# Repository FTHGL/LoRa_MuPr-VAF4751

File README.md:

# Multi-Protocol Hybrid Wireless Communication System (LoRa-GSM-DTMF)

An **STM32-based hybrid communication platform** designed for seamless data and command transmission in environments with limited or no internet infrastructure (disaster management, rural IoT, remote monitoring or etc.). This system integrates low-power **LoRa** technology with **GSM** coverage and **DTMF** control into a single modular architecture.

## Technical Architecture
The system utilizes a hybrid topology consisting of a **Master** node and multiple **Slave** nodes:

* **Master Node:** Features an STM32F103C8T6 MCU, SIM800C GSM module, and RN2483A LoRa module. It acts as the network gateway and central authority.
* **Slave Nodes:** Composed of STM32F103C8T6 and RN2483A modules. These nodes collect sensor data and transmit it to the Master via LoRa.
* **Hybrid Topology:** Operates in a "Star" configuration under normal conditions, with a dynamic shift to a "Mesh" structure using nodes as opportunistic relays when direct access is obstructed.

## Key Features
* **Protocol Bridging:** Real-time translation of commands received via SMS or Command (DTMF) into LoRa packets for end-node execution.
* **Fault Tolerance:** Dynamic routing mechanism allowing slave nodes to reach the master through neighboring nodes if the direct link is lost.
* **Critical Control (DTMF):** Infrastructure-independent device management via voice calls and DTMF tones, bypassing the need for internet or SMS data lines.
* **RF Optimization:** Impedance-controlled transmission lines (50 Ω) and custom antenna structures optimized for 868 MHz and 1.8 GHz bands.

## Hardware Specifications
* **MCU:** STM32F103C8T6 (ARM Cortex-M3).
* **RF Modules:** Microchip RN2483A (LoRa), SIMCom SIM800C (GSM/GPRS/DTMF).
* **Antenna Design:** Integrated IFA (Inverted-F Antenna) for 868 MHz and optimized microstrip structures for 1.8 GHz.
* **PCB Design:** High RF integrity with dedicated ground planes and impedance-matched traces.

## Software Flow
The firmware is modular, managing cross-protocol data flow and task scheduling:
1.  **Ingress:** Command reception and validation via GSM (SMS/DTMF).
2.  **Routing:** Identification of the target `node_id` and LoRa packet encapsulation.
3.  **Transmission:** Delivery of data to the slave node and reporting the response (ACK/Data) back to the user via GSM.

---
*This project was developed as a Graduation Project at Konya Technical University, Department of Electrical and Electronics Engineering.*

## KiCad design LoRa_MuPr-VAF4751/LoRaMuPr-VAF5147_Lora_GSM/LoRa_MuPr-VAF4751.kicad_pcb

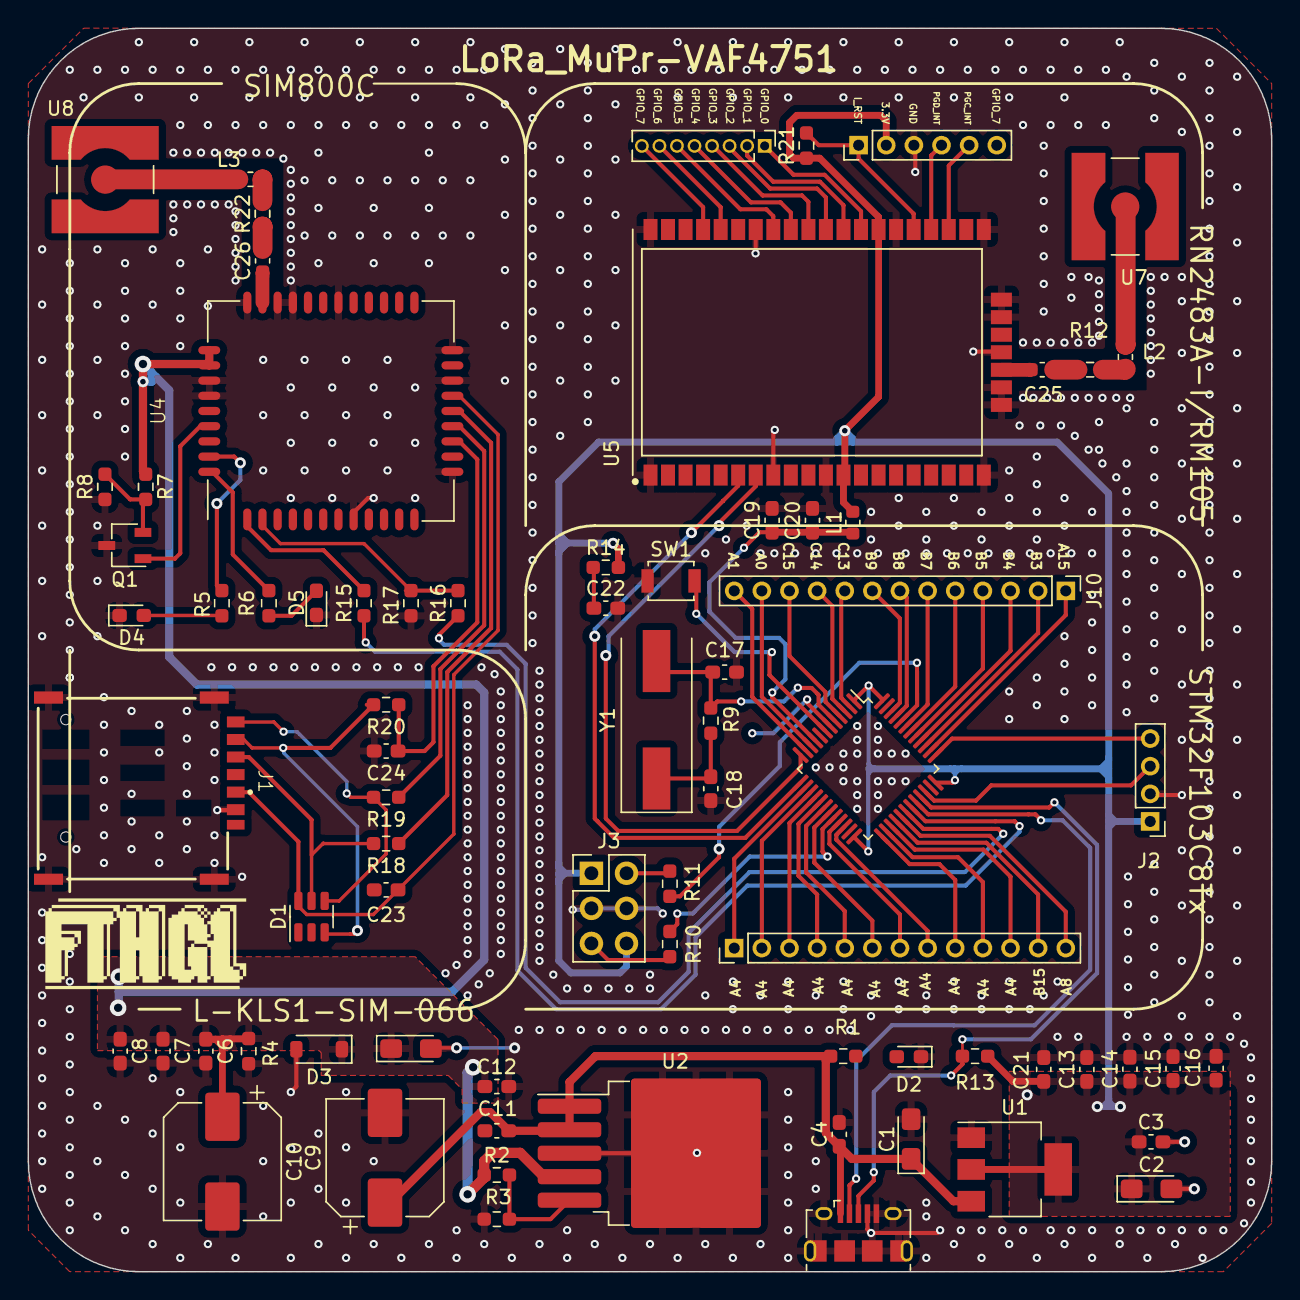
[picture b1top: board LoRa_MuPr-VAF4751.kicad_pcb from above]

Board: 2 copper layers, 90.0 x 90.0 mm, 74 parts (0 on the bottom side), 83 nets.

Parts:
C1, C2: 10uF; CP_EIA-3216-18_Kemet-A_Pad1.58x1.35mm_HandSolder
C3, C4, C13, C14, C15, C16, C20, C22, C23: 100nF; C_0603_1608Metric_Pad1.08x0.95mm_HandSolder
C5: 100uF; CP_EIA-3216-18_Kemet-A_Pad1.58x1.35mm_HandSolder
C6, C12: 10uF; C_0603_1608Metric_Pad1.08x0.95mm_HandSolder
C7: 33pF; C_0603_1608Metric_Pad1.08x0.95mm_HandSolder
C8: 10pF; C_0603_1608Metric_Pad1.08x0.95mm_HandSolder
C9: 100uF; CP_Elec_8x10
C10: 330uF; CP_Elec_8x10
C11, C19: 1uF; C_0603_1608Metric_Pad1.08x0.95mm_HandSolder
C17, C18, C24: 22pF; C_0603_1608Metric_Pad1.08x0.95mm_HandSolder
C21: 4u7F; C_0603_1608Metric_Pad1.08x0.95mm_HandSolder
C25: 9.1pF; C_0603_1608Metric_Pad1.08x0.95mm_HandSolder
C26: 1.8pF; C_0603_1608Metric_Pad1.08x0.95mm_HandSolder
D1: ESDA6V1-5SC6; SOT-23-6
D2, D4, D5: LED; LED_0603_1608Metric_Pad1.05x0.95mm_HandSolder
D3: 5.1V/500mW; D_SOD-123
J1: SIM_Card; L-KLS1-SIM-066
J2: Conn_01x04; PinHeader_1x04_P2.00mm_Vertical
J3: Conn_02x03_Counter_Clockwise; PinHeader_2x03_P2.54mm_Vertical
J5: Conn_01x06; PinHeader_1x06_P2.00mm_Vertical
J6: Conn_01x08; PinHeader_1x08_P1.27mm_Vertical
J10, J11: Conn_01x13; PinHeader_1x13_P2.00mm_Vertical
L1: 27nH; L_0603_1608Metric
L2: 4.7nH; L_0603_1608Metric_Pad1.05x0.95mm_HandSolder
L3: 3.9nH; L_0603_1608Metric_Pad1.05x0.95mm_HandSolder
Q1: BC337; TSOT-23
R1, R5, R6, R10, R11: 1k; R_0603_1608Metric_Pad0.98x0.95mm_HandSolder
R2: 100k; R_0603_1608Metric_Pad0.98x0.95mm_HandSolder
R3: 43k; R_0603_1608Metric_Pad0.98x0.95mm_HandSolder
R4: 470R; R_0603_1608Metric_Pad0.98x0.95mm_HandSolder
R7, R8: 4.7k; R_0603_1608Metric_Pad0.98x0.95mm_HandSolder
R9: 1M; R_0603_1608Metric_Pad0.98x0.95mm_HandSolder
R12, R22: 50R; R_0603_1608Metric_Pad0.98x0.95mm_HandSolder
R13, R14: 1k5; R_0603_1608Metric_Pad0.98x0.95mm_HandSolder
R15, R16: 1K; R_0603_1608Metric_Pad0.98x0.95mm_HandSolder
R17: 5.6K; R_0603_1608Metric_Pad0.98x0.95mm_HandSolder
R18, R19, R20: 51R; R_0603_1608Metric_Pad0.98x0.95mm_HandSolder
R21: 10k; R_0603_1608Metric_Pad0.98x0.95mm_HandSolder
SW1: SW_Push; SW_SPST_B3U-1000P
U1: AMS1117-3.3; SOT-223-3_TabPin2
U2: MIC29302WU; TO-263-5_TabPin3
U3: STM32F103C8Tx; LQFP-48_7x7mm_P0.5mm
U4: SIM800C; SİM800C
U5: RN2483A-I/RM105; MICROCHIP_RN2483
U6: USB_micro-B_amphenol; USB_micro-B_amphenol_101181994_horizontal
U7, U8: LINX_CONSMA001-SMD
Y1: Crystall; Crystal_SMD_HC49-SD

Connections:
3.3V: C2.1, C3.1, C13.1, C14.1, C15.1, C16.1, C21.1, J2.1, J3.1, J3.6, J5.2, L1.1, R13.2, R14.2, R21.1, U1.2 (VO), U3.1 (VBAT), U3.24 (VDD), U3.36 (VDD), U3.48 (VDD), U5.12 (VDD), U5.34 (VDD)
3.3VA: C19.1, C20.1, L1.2, U3.9 (VDDA)
5v: C1.1, C4.1, C9.1, C11.1, R1.1, U1.3 (VI), U2.1 (EN), U2.2 (VIN), U6.1 (VBUS)
BOOT_0: R11.1, U3.44 (BOOT0)
BOOT_1: R10.2, U3.20 (PB2)
GND: C1.2, C2.2, C3.2, C4.2, C5.2, C6.2, C7.2, C8.2, C9.2, C10.2, C11.2, C12.2, C13.2, C14.2, C15.2, C16.2, C17.1, C18.1, C19.2, C20.2, C21.2, C22.2, C23.2, C24.1, D1.2 (GND), D2.1 (K), D3.2 (A), D4.1 (K), D5.1 (K), J1.5 (GND), J2.2, J3.3, J3.4, J5.3, Q1.3 (E), R3.2, R4.2, R8.1, R17.1, SW1.2, U1.1 (GND), U2.3 (GND), U3.8 (VSSA), U3.23 (VSS), U3.35 (VSS), U3.47 (VSS), U4.8 (GND), U4.13 (GND), U4.19 (GND), U4.21 (GND), U4.27 (GND), U4.30 (GND), U4.31 (GND), U4.33 (GND), U4.36 (GND), U4.37 (GND), U5.1 (GND), U5.8 (GND), U5.11 (GND), U5.20 (GND), U5.21 (GND), U5.22 (GND), U5.24 (GND), U5.26 (GND), U5.27 (GND), U5.28 (GND), U5.33 (GND), U5.41 (GND), U5.47 (GND), U6.4 (ID), U6.5 (GND), U6.6 (Shield)
GSM_ANT: C26.1, U4.32 (GSM_ANT)
HSE_OSC_IN: C17.2, R9.1, U3.5 (PD0), Y1.2
HSE_OSC_OUT: C18.2, R9.2, U3.6 (PD1), Y1.1
I_RESET: J5.1, R21.2, U5.32 (*RESET)
L_GPIO0: J6.1, U5.35 (GPIO0)
L_GPIO1: J6.2, U5.36 (GPIO1)
L_GPIO2: J6.3, U5.37 (GPIO2)
L_GPIO3: J6.4, U5.38 (GPIO3)
L_GPIO4: J6.5, U5.39 (GPIO4)
L_GPIO5: J6.6, U5.40 (GPIO5)
L_GPIO6: J6.7, U5.43 (GPIO6)
L_GPIO7: J6.8, U5.44 (GPIO7)
unnamed: C22.1, R14.1
unnamed: C25.2, R12.1
unnamed: C26.2, R22.1
unnamed: D1.3 (IO2), J1.7 (I/O), R20.1
unnamed: D1.4 (IO3), J1.3 (CLK), R19.2
unnamed: D1.5 (IO4), J1.2 (RST), R18.2
unnamed: D2.2 (A), R1.2
unnamed: D4.2 (A), R5.2
unnamed: D5.2 (A), R6.2
unnamed: J3.2, R11.2
unnamed: J3.5, R10.1
unnamed: L2.1, R12.2
unnamed: L3.2, R22.2
unnamed: Q1.2 (B), R7.2, R8.2
unnamed: R2.2, R3.1, U2.5 (ADJ)
unnamed: R5.1, U4.41 (NETLIGHT)
unnamed: R6.1, U4.42 (STATUS)
unnamed: C25.1, U5.23 (RFH)
unnamed: L2.2, U7.1 (In)
unnamed: L3.1, U8.1 (In)
P13: J10.9, U3.2 (PC13)
PA0: J10.12, U3.10 (PA0)
PA1: J10.13, U3.11 (PA1)
PA4: J11.1, U3.14 (PA4)
PA5: J11.2, U3.15 (PA5)
PA6: J11.3, U3.16 (PA6)
PA7: J11.4, U3.17 (PA7)
PA8: J11.13, U3.29 (PA8)
PA15: J10.1, U3.38 (PA15)
PB0: J11.5, U3.18 (PB0)
PB1: J11.6, U3.19 (PB1)
PB3: J10.2, U3.39 (PB3)
PB4: J10.3, U3.40 (PB4)
PB5: J10.4, U3.41 (PB5)
PB6: J10.5, U3.42 (PB6)
PB7: J10.6, U3.43 (PB7)
PB8: J10.7, U3.45 (PB8)
PB9: J10.8, U3.46 (PB9)
PB10: J11.7, U3.21 (PB10)
PB11: J11.8, U3.22 (PB11)
PB12: J11.9, U3.25 (PB12)
PB13: J11.10, U3.26 (PB13)
PB14: J11.11, U3.27 (PB14)
PB15: J11.12, U3.28 (PB15)
PC14: J10.10, U3.3 (PC14)
PC15: J10.11, U3.4 (PC15)
PGC_INT: J5.5, U5.30 (PGC_INT)
PGD_INT: J5.4, U5.31 (PGD_INT)
PWRKEY: Q1.1 (C), U4.39 (~PWRKEY)
RESET: SW1.1, U3.7 (NRST)
SIM_CLK: R19.1, U4.16 (SIM_CLK)
SIM_DATA: C24.2, R20.2, U4.15 (SIM_DATA)
SIM_RST: R18.1, U4.17 (SIM_RST)
SIM_UART1_RXD: R16.2, R17.2, U4.2 (UART1_RXD)
SIM_UART1_TXD: R15.2, U4.1 (UART1_TXD)
SIM_VDD: C23.1, D1.6 (IO5), J1.1 (VCC), U4.18 (SIM_VDD)
SWDCLK: J2.4, U3.37 (PA14)
SWDIO: J2.3, U3.34 (PA13)
USART1_RX: R15.1, U3.31 (PA10)
USART1_TX: R16.1, U3.30 (PA9)
USART2_RX: U3.13 (PA3), U5.6 (UART_TX)
USART2_TX: U3.12 (PA2), U5.7 (UART_RX)
USB_DN: U3.32 (PA11), U6.2 (D-)
USB_DP: R13.1, U3.33 (PA12), U6.3 (D+)
VBAT: C5.1, C6.1, C7.1, C8.1, C10.1, C12.1, D3.1 (K), R2.1, R4.1, R7.1, U2.4 (VOUT), U4.34 (VBAT), U4.35 (VBAT)

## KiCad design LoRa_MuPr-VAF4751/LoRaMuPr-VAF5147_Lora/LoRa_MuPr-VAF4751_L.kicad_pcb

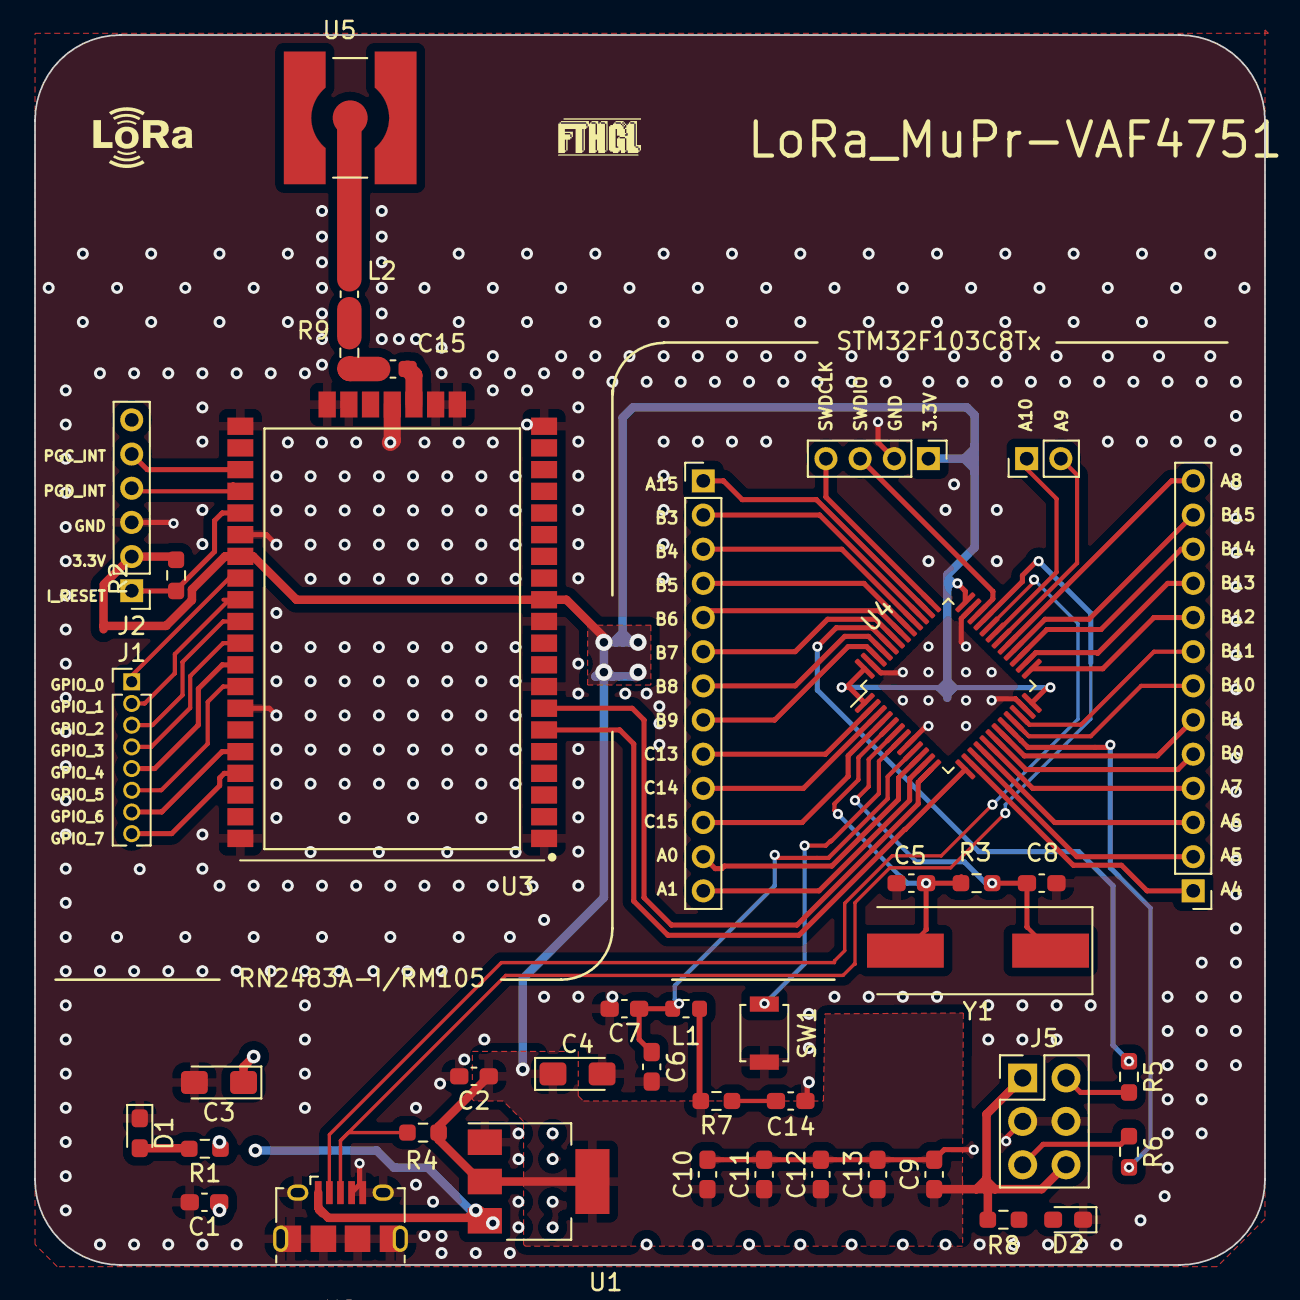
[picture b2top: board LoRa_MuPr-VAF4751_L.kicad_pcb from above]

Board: 2 copper layers, 72.0 x 72.0 mm, 42 parts (0 on the bottom side), 63 nets.

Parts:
C1, C2, C7, C10, C11, C12, C13, C14: 100nF; C_0603_1608Metric_Pad1.08x0.95mm_HandSolder
C3, C4: 10uF; CP_EIA-3216-18_Kemet-A_Pad1.58x1.35mm_HandSolder
C5, C8: 22pF; C_0603_1608Metric_Pad1.08x0.95mm_HandSolder
C6: 1uF; C_0603_1608Metric_Pad1.08x0.95mm_HandSolder
C9: 4u7F; C_0603_1608Metric_Pad1.08x0.95mm_HandSolder
C15: 9.1pF; C_0603_1608Metric_Pad1.08x0.95mm_HandSolder
D1, D2: LED; LED_0603_1608Metric_Pad1.05x0.95mm_HandSolder
J1: Conn_01x08; PinHeader_1x08_P1.27mm_Vertical
J2: Conn_01x06; PinHeader_1x06_P2.00mm_Vertical
J4: Conn_01x04; PinHeader_1x04_P2.00mm_Vertical
J5: Conn_02x03_Counter_Clockwise; PinHeader_2x03_P2.54mm_Vertical
J6, J7: Conn_01x13; PinHeader_1x13_P2.00mm_Vertical
J8: Conn_01x02; PinHeader_1x02_P2.00mm_Vertical
L1: 27nH; L_0603_1608Metric
L2: 4.7nH; L_0603_1608Metric_Pad1.05x0.95mm_HandSolder
R1, R5, R6, R8: 1k; R_0603_1608Metric_Pad0.98x0.95mm_HandSolder
R2: 10k; R_0603_1608Metric_Pad0.98x0.95mm_HandSolder
R3: 1M; R_0603_1608Metric_Pad0.98x0.95mm_HandSolder
R4, R7: 1k5; R_0603_1608Metric_Pad0.98x0.95mm_HandSolder
R9: 50R; R_0603_1608Metric_Pad0.98x0.95mm_HandSolder
SW1: SW_Push; SW_SPST_B3U-1000P
U1: AMS1117-3.3; SOT-223-3_TabPin2
U2: USB_micro-B_amphenol; USB_micro-B_amphenol_101181994_horizontal
U3: RN2483A-I/RM105; MICROCHIP_RN2483
U4: STM32F103C8Tx; LQFP-48_7x7mm_P0.5mm
U5: LINX_CONSMA001-SMD
Y1: Crystall; Crystal_SMD_HC49-SD

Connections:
3.3V: C2.1, C4.1, C9.1, C10.1, C11.1, C12.1, C13.1, J2.2, J4.1, J5.1, J5.6, L1.1, R2.1, R4.2, R7.2, R8.1, U1.2 (VO), U3.12 (VDD), U3.34 (VDD), U4.1 (VBAT), U4.24 (VDD), U4.36 (VDD), U4.48 (VDD)
3.3VA: C6.1, C7.1, L1.2, U4.9 (VDDA)
5v: C1.1, C3.1, R1.1, U1.3 (VI), U2.1 (VBUS)
BOOT_0: R5.1, U4.44 (BOOT0)
BOOT_1: R6.2, U4.20 (PB2)
GND: C1.2, C2.2, C3.2, C4.2, C5.1, C6.2, C7.2, C8.1, C9.2, C10.2, C11.2, C12.2, C13.2, C14.2, D1.1 (K), D2.1 (K), J2.3, J4.2, J5.3, J5.4, SW1.2, U1.1 (GND), U2.4 (ID), U2.5 (GND), U2.6 (Shield), U3.1 (GND), U3.8 (GND), U3.11 (GND), U3.20 (GND), U3.21 (GND), U3.22 (GND), U3.24 (GND), U3.26 (GND), U3.27 (GND), U3.28 (GND), U3.33 (GND), U3.41 (GND), U3.47 (GND), U4.8 (VSSA), U4.23 (VSS), U4.35 (VSS), U4.47 (VSS)
HSE_OSC_IN: C5.2, R3.1, U4.5 (PD0), Y1.2
HSE_OSC_OUT: C8.2, R3.2, U4.6 (PD1), Y1.1
I_RESET: J2.1, R2.2, U3.32 (*RESET)
L_GPIO0: J1.1, U3.35 (GPIO0)
L_GPIO1: J1.2, U3.36 (GPIO1)
L_GPIO2: J1.3, U3.37 (GPIO2)
L_GPIO3: J1.4, U3.38 (GPIO3)
L_GPIO4: J1.5, U3.39 (GPIO4)
L_GPIO5: J1.6, U3.40 (GPIO5)
L_GPIO6: J1.7, U3.43 (GPIO6)
L_GPIO7: J1.8, U3.44 (GPIO7)
unnamed: C14.1, R7.1
unnamed: C15.1, R9.1
unnamed: D1.2 (A), R1.2
unnamed: D2.2 (A), R8.2
unnamed: J5.2, R5.2
unnamed: J5.5, R6.1
unnamed: L2.1, R9.2
unnamed: C15.2, U3.23 (RFH)
unnamed: L2.2, U5.1 (In)
P13: J6.9, U4.2 (PC13)
PA0: J6.12, U4.10 (PA0)
PA1: J6.13, U4.11 (PA1)
PA4: J7.1, U4.14 (PA4)
PA5: J7.2, U4.15 (PA5)
PA6: J7.3, U4.16 (PA6)
PA7: J7.4, U4.17 (PA7)
PA8: J7.13, U4.29 (PA8)
PA15: J6.1, U4.38 (PA15)
PB0: J7.5, U4.18 (PB0)
PB1: J7.6, U4.19 (PB1)
PB3: J6.2, U4.39 (PB3)
PB4: J6.3, U4.40 (PB4)
PB5: J6.4, U4.41 (PB5)
PB6: J6.5, U4.42 (PB6)
PB7: J6.6, U4.43 (PB7)
PB8: J6.7, U4.45 (PB8)
PB9: J6.8, U4.46 (PB9)
PB10: J7.7, U4.21 (PB10)
PB11: J7.8, U4.22 (PB11)
PB12: J7.9, U4.25 (PB12)
PB13: J7.10, U4.26 (PB13)
PB14: J7.11, U4.27 (PB14)
PB15: J7.12, U4.28 (PB15)
PC14: J6.10, U4.3 (PC14)
PC15: J6.11, U4.4 (PC15)
PGC_INT: J2.5, U3.30 (PGC_INT)
PGD_INT: J2.4, U3.31 (PGD_INT)
RESET: SW1.1, U4.7 (NRST)
SWDCLK: J4.4, U4.37 (PA14)
SWDIO: J4.3, U4.34 (PA13)
USART1_RX: J8.1, U4.31 (PA10)
USART1_TX: J8.2, U4.30 (PA9)
USART2_RX: U3.6 (UART_TX), U4.13 (PA3)
USART2_TX: U3.7 (UART_RX), U4.12 (PA2)
USB_DN: U2.2 (D-), U4.32 (PA11)
USB_DP: R4.1, U2.3 (D+), U4.33 (PA12)

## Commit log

2023-12-23 upload Flowchart
2024-05-19 HFSS documents
2024-07-08 LoRaMuPr-VAF5147 files uploaded
2024-07-08 Rename SİM800C.kicad_sch to SIM800C.kicad_sch
    .
2026-01-12 Revise README for project overview and technical details
    Updated project title and description to reflect a broader scope and technical details. Enhanced feature list and clarified hardware specifications.
